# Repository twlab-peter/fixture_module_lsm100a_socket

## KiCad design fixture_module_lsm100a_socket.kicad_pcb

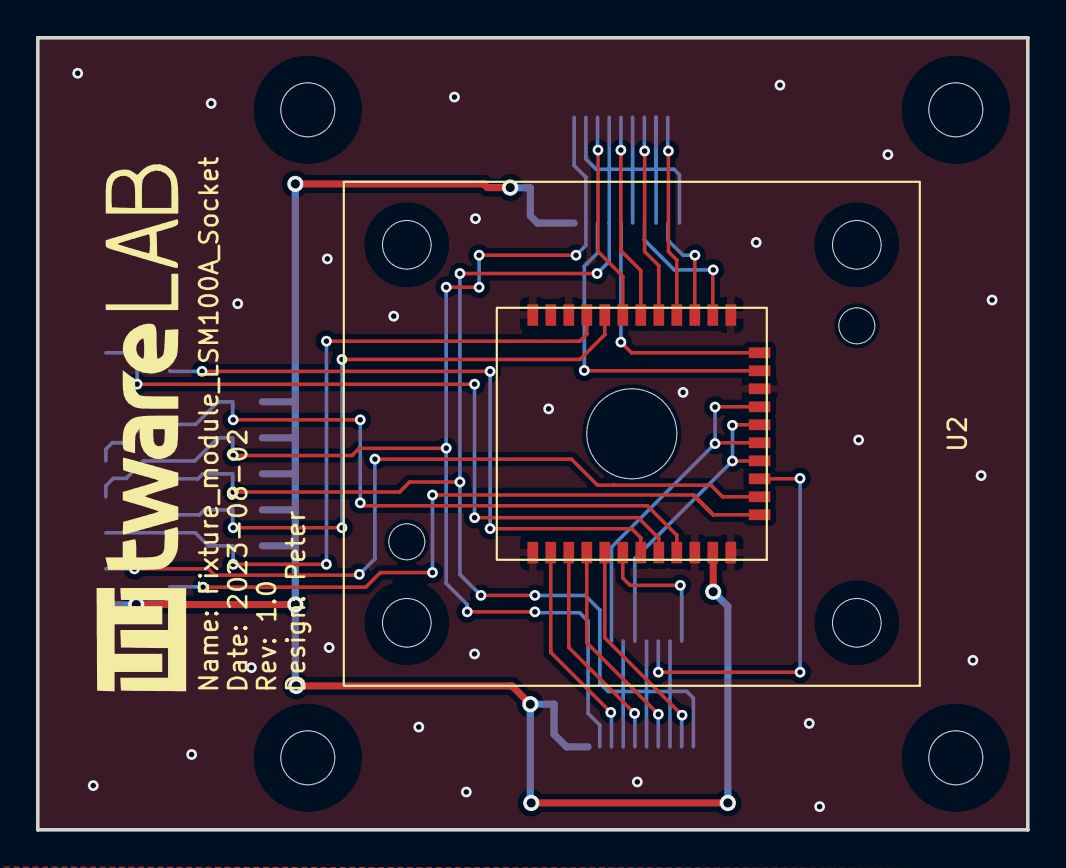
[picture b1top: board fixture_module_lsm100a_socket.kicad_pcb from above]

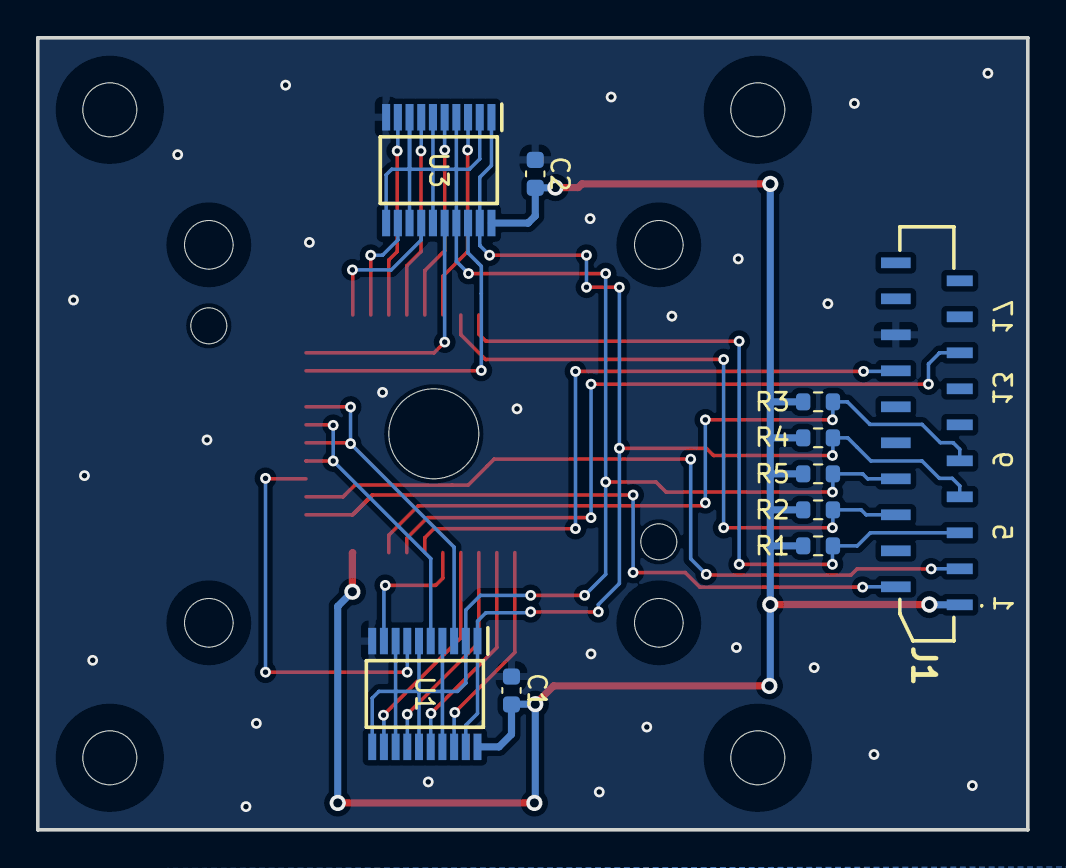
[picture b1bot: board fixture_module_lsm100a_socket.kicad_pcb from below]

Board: 2 copper layers, 55.0 x 44.0 mm, 11 parts (10 on the bottom side), 27 nets.

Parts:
C1, C2: 1uF; C_0603_1608Metric
J1: Conn_01x20; 528082071
R1, R2, R3, R4, R5: 10K; R_0603_1608Metric
U1, U3: SN74LVC240APW; SOP65P640X120-20N
U2: LSM100A_SOCKET; lsm100a_socket

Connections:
/LSM100A_WITH_SOCKET/TIO0: U1.18 (1Y1), U2.2 (PB2)
/LSM100A_WITH_SOCKET/TIO1: U1.16 (1Y2), U2.3 (PA9)
/LSM100A_WITH_SOCKET/TIO2: U1.14 (1Y3), U2.4 (PA10)
/LSM100A_WITH_SOCKET/TIO3: U1.12 (1Y4), U2.5 (PA11)
/LSM100A_WITH_SOCKET/TIO4: U1.9 (2Y1), U2.6 (PA12)
/LSM100A_WITH_SOCKET/TIO5: U1.7 (2Y2), U2.15 (PA1)
/LSM100A_WITH_SOCKET/TIO6: U1.5 (2Y3), U2.16 (PA0), U2.18 (PB7/U1RX)
/LSM100A_WITH_SOCKET/TIO7: U1.3 (2Y4), U2.17 (PB8), U2.19 (PB6/U1TX)
/LSM100A_WITH_SOCKET/TIO8: U2.21 (PB3), U3.18 (1Y1)
/LSM100A_WITH_SOCKET/TIO9: U2.22 (PB4), U3.16 (1Y2)
/LSM100A_WITH_SOCKET/TIO10: U2.24 (PA8), U3.14 (1Y3)
/LSM100A_WITH_SOCKET/TIO11: U2.25 (PA7), U3.12 (1Y4)
/LSM100A_WITH_SOCKET/TIO12: U2.26 (PB5), U3.9 (2Y1)
/LSM100A_WITH_SOCKET/TIO13: U2.27 (PA6), U3.7 (2Y2)
/LSM100A_WITH_SOCKET/TIO14: U2.28 (PA5), U3.5 (2Y3)
/LSM100A_WITH_SOCKET/TIO15: U2.29 (PA4), U3.3 (2Y4)
GND: C1.2, C2.2, J1.16, U1.10 (GND), U2.1 (GND), U2.10 (GND), U2.12 (GND), U2.20 (GND), U2.23 (GND), U2.32 (GND), U2.34 (GND), U3.10 (GND)
GPIO02: J1.5, R1.2, U2.31 (BOOT)
GPIO03: J1.6, R2.2, U2.30 (NRST)
GPIO04: J1.7, R4.2, U1.1 (1~OE), U1.19 (2~OE), U3.1 (1~OE), U3.19 (2~OE)
GPIO05: J1.8, R5.2, U1.2 (1A1), U1.4 (1A2), U1.6 (1A3), U1.8 (1A4), U1.11 (2A1), U1.13 (2A2), U1.15 (2A3), U1.17 (2A4), U3.2 (1A1), U3.4 (1A2), U3.6 (1A3), U3.8 (1A4), U3.11 (2A1), U3.13 (2A2), U3.15 (2A3), U3.17 (2A4)
GPIO06: J1.9, R3.2, U2.9 (PA15)
SWCLK: J1.15, U2.8 (PA14/SWCLK)
SWDIO: J1.14, U2.7 (PA13/SWDIO)
UART2_RX: J1.3, U2.14 (PA2/U2TX)
UART2_TX: J1.2, U2.13 (PA3/U2RX)
VDD: C1.1, C2.1, J1.1, R1.1, R2.1, R3.1, R4.1, R5.1, U1.20 (VCC), U2.11 (VDD), U3.20 (VCC)
